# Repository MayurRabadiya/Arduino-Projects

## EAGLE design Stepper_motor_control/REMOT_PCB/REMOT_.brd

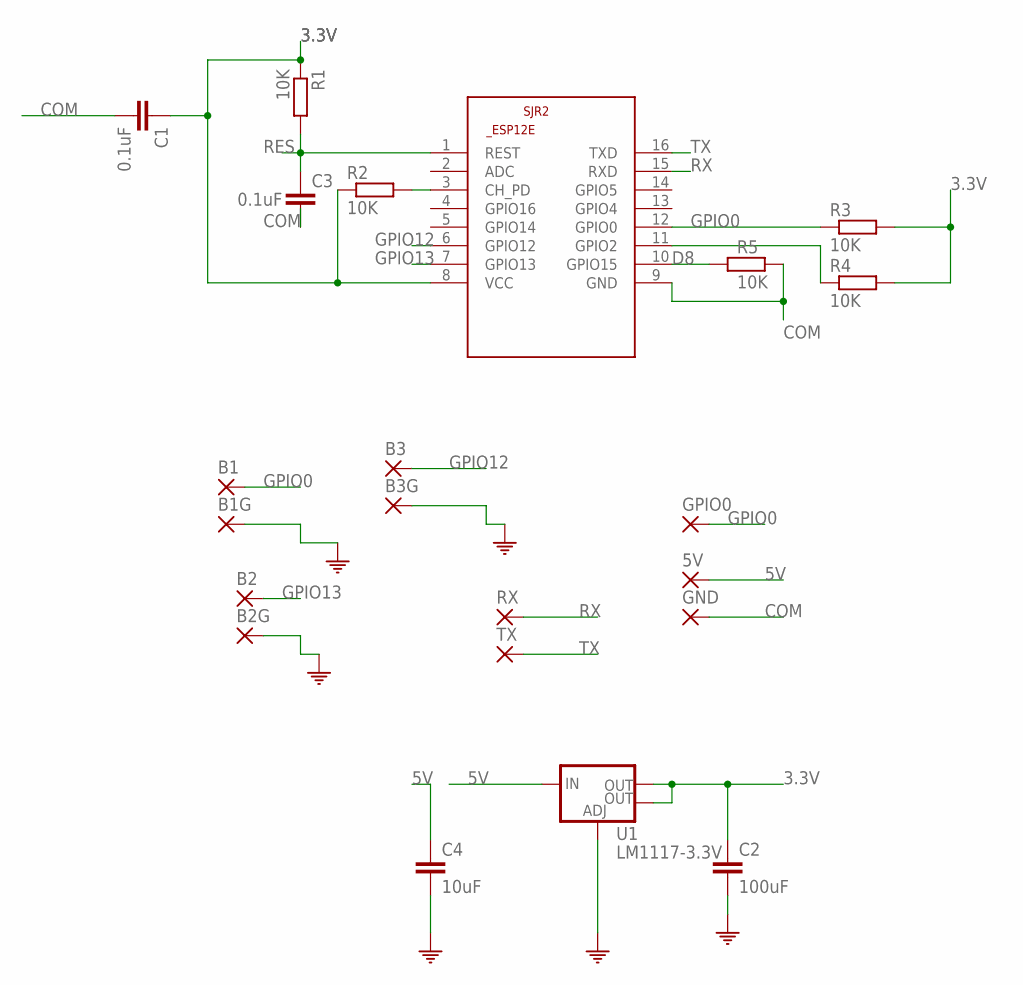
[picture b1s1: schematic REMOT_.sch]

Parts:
5V: SMD2; SMD1,27-2,54
B1, B2, B2G, B3, B3G: SMD2; SMD1,27-2,54
B1G: COM; SMD1,27-2,54
C1, C3: 0.1uF; C1206
C2: 100uF; C1206
C4: 10uF; C1206
GND: SMD2; SMD1,27-2,54
GPIO0: SMD2; SMD1,27-2,54
R1, R2, R3, R4, R5: 10K; R0805
RX: SMD2; SMD1,27-2,54
SJR2: ESP8266-12EESP12E; ESP8266-ESP12E
TX: SMD2; SMD1,27-2,54
U1: LM1117-3.3V; SOT223

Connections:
3.3V: C1.1, C2.1, R1.1, R2.1, R3.2, R4.2, SJR2.8 (VCC), U1.2 (OUT), U1.4 (OUT)
5V: 5V.1, C4.1, U1.3 (IN)
COM: B1G.1, B2G.1, B3G.1, C1.2, C2.2, C3.2, C4.2, GND.1, R5.2, SJR2.9 (GND), U1.1 (ADJ)
D8: R5.1, SJR2.10 (GPIO15)
GPIO0: B1.1, GPIO0.1, R3.1, SJR2.12 (GPIO0)
GPIO12: B3.1, SJR2.6 (GPIO12)
GPIO13: B2.1, SJR2.7 (GPIO13)
unnamed: R4.1, SJR2.11 (GPIO2)
unnamed: R2.2, SJR2.3 (CH_PD)
RES: C3.1, R1.2, SJR2.1 (REST)
RX: RX.1, SJR2.15 (RXD)
TX: SJR2.16 (TXD), TX.1

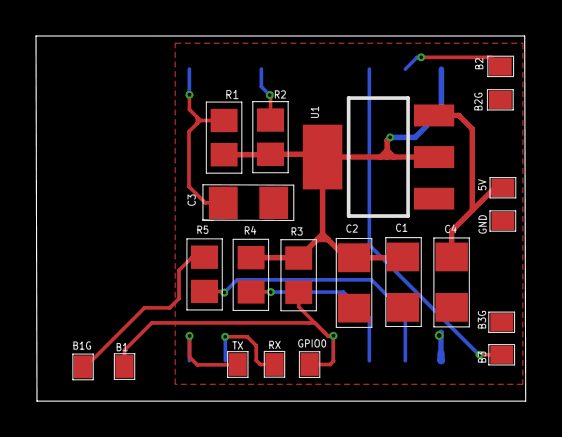
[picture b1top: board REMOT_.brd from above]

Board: 2 copper layers, 27.2 x 20.3 mm, 22 parts (1 on the bottom side), 12 nets.

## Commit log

2024-07-15 Project_added

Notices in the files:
parts and their libraries:
SparkFun-IC-Power: Licensing: Creative Commons ShareAlike 4.0 International - https://creativecommons.org/licenses/by-sa/4.0
